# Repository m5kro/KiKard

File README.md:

# KiKard
Pronounced key card. KiKard is a usb microcontroller board with NFC read, write, and tag support. Built for Hack Club Highway. Not affiliated with KiCad (but do check them out).<br>
<br>

# What it does
KiKard is designed to read, write, and emulate NFC devices. This can be anything from simple link tags to complex keycards with custom communication standards. It can work independently or with a computer through BLE or USB.

# Why I built it
The goal of this project is to create a tool to assist me with my NFC application development learning. About a year ago, I wanted to make apps that utilize NFC, but I realized that most phones (most widespread implementation of NFC) are terrible for the development process as everything is very locked down. I did get a cheap PN532 reader from amazon and while it did help, it was still very lacking. Thus I decided to create KiKard to cover all the requirements needed by my other projects.

# Other Notes
Although the NRF has NFC support built in, it's only for tag mode, so a separate chip is needed for reading NFC.<br>
RGB LED 1 - Status led Green: just connected, Pink: reset/flashing, Blue: NRF52 tag mode, Yellow: ST25 read mode, Red: error<br>
RGB LED 2 - read/tag status Yellow: waiting, Blue: reading/emulating, Green: success, Red: error<br>
Button 1 - Read/emulate<br>
Button 2 - Switch between NRF52 and ST25<br>
Button 3 - Switch emulated tag (can save different cards on device)<br>
The DAPLINK is used to flash the NRF with a bootloader as it doesn't come with one by default. There are test pads on the board to connect.<br>
There are alot of extended parts as I needed high quality caps for the NFC antenna.<br>
Tariffs are making this project alot more expensive than it needs to be ;(

# Bom
| Item | Price |
| :-----: | :-----: |
| Custom PCB x5 | $4.00 |
| PCBA Setup | $8.00 |
| Stencil | $1.50 |
| PCB Parts x2| $20.07
| Extended Parts Fee | $81.00 |
| SMT Assembly | $1.86
| X-ray Inspection (required) | $3.14 |
| Nitrogen Reflow Soldering | $0.82 |
| Shipping | $28.85 |
| Customs | $66.22 |
| [DAPLINK](https://www.aliexpress.us/item/3256803753392042.html?spm=a2g0o.productlist.main.3.3b9aeQixeQixOW&algo_pvid=7bf879f9-2744-4cec-8234-a12f393fd66a&algo_exp_id=7bf879f9-2744-4cec-8234-a12f393fd66a-2&pdp_ext_f=%7B%22order%22%3A%2246%22%2C%22eval%22%3A%221%22%7D&pdp_npi=4%40dis%21USD%212.61%210.99%21%21%212.61%210.99%21%402101eac917534651461111152e6da5%2112000027518372890%21sea%21US%210%21ABX&curPageLogUid=WIV7fF3EkrpJ&utparam-url=scene%3Asearch%7Cquery_from%3A) | $3.52 |
| JLCPCB special discount | -$2.00 |

**Total: $227.50**

# PCB Parts Bom (PER PCB)
Total PCB Parts: 71<br>
Total PCB Parts Price (per PCB): $8.7174
| Part | Designator | Quantity | Price per Unit | Total | JLCPCB/LCSC Part No. |
| :---------: | :-----: | :-----: | :-----: | :-----: | :-----: |
| [NRF-52840-QIAA-R](https://jlcpcb.com/partdetail/NordicSemicon-NRF52840_QIAAR/C190794) | U1 | 1 | $4.0290 | $4.0290 | C190794 |
| [ST25R3916-AQWT](https://jlcpcb.com/partdetail/STMicroelectronics-ST25R3916AQWT/C2908147) | U2 | 1 | $3.3795 | $3.3795 | C2908147 |
| [WNM3013-3/TR](https://jlcpcb.com/partdetail/WILLSEMI_Will_Semicon-WNM3013_3TR/C239659) | Q1, Q2 | 2 | $0.0333 | $0.0667 | C239659 |
| [32MHz Crystal Oscillator](https://jlcpcb.com/partdetail/2777870-X201632MOB4SI/C2682773) | Y2 | 1 | $0.0890 | $0.0890 | C2682773 |
| [27MHz Crystal Oscillator](https://jlcpcb.com/partdetail/604049-XRCGB27M120F3M00R0/C576558) | Y1 | 1 | $0.1773 | $0.1773 | C576558 |
| [32KHz Crystal Oscillator](https://jlcpcb.com/partdetail/357119-X161032768KGD2SI/C383847) | Y3 | 1 | $0.3825 | $0.3825 | C383847 |
| [USB-C Port](https://jlcpcb.com/partdetail/SHOUHAN-TYPEC16PIN/C393939) | USB1 | 1 | $0.0642 | $0.0642 | C393939 |
| [RGBLED](https://jlcpcb.com/partdetail/ChauLight-ZSRGB_2017H_08Z3/C7497245) | LED1, LED2 | 2 | $0.0807 | $0.1614 | C7497245 |
| [Button](https://jlcpcb.com/partdetail/Korean_HropartsElec-K2_6639SP_C4SC04/C83206) | SW1, SW2, SW3 | 3 | $0.0380 | $0.1140 | C83206 |
| [Small Button](https://jlcpcb.com/partdetail/hanxia-HX_3x4x2_2P_25N/C36498961) | SW4 | 1 | $0.0299 | $0.0299 | C36498961 |
| [100k Ohm Resistor](https://jlcpcb.com/partdetail/YAGEO-RC0603FR07100KL/C14675) | R3, R4 | 2 | $0.0010 | $0.0020 | C14675 |
| [10k Ohm Resistor](https://jlcpcb.com/partdetail/26274-0402WGJ0103TCE/C25531) | R5 | 1 | $0.0004 | $0.0004 | C25531 |
| [5.1k Ohm Resistor](https://jlcpcb.com/partdetail/26684-0402WGJ0512TCE/C25941) | R1, R2 | 2 | $0.0004 | $0.0008 | C25941 |
| [4.7uF Capacitor](https://jlcpcb.com/partdetail/20375-CL10A475KO8NNNC/C19666) | C1, C2, C3, C32 | 4 | $0.0101 | $0.0404 | C19666 |
| [2.2uF Capacitor](https://jlcpcb.com/partdetail/1959-CL10A225KP8NNNC/C1607) | C5, C7, C9, C13, C15, C17, C19 | 7 | $0.0060 | $0.0420 | C1607 |
| [1uF Capacitor](https://jlcpcb.com/partdetail/15107-CL05A105KP5NNNC/C14445) | C11, C27 | 2 | $0.0016 | $0.0032 | C14445 |
| [100nF Capacitor](https://jlcpcb.com/partdetail/57421-0402B104K250NT/C56392) | C28, C29, C30, C31, C34, C47 | 6 |  $0.0011 |  $0.0066 | C56392 |
| [47nF Capacitor](https://jlcpcb.com/partdetail/83376-0402B473K500NT/C82219) | C26 | 1 | $0.0017 | $0.0017 | C82219 |
| [10nF Capacitor](https://jlcpcb.com/partdetail/1876-0402B103K500NT/C1524) | C4, C6, C8, C10, C12, C14, C16, C18 | 8 | $0.0010 | $0.0080 | C1524 |
| [1nF Capacitor](https://jlcpcb.com/partdetail/TDK-C1005C0G1E102JT000F/C343059) | C45, C46 | 2 | $0.0089 | $0.0178 | C343059 |
| [680pF Capacitor](https://jlcpcb.com/partdetail/1893-0402B681K500NT/C1541) | C38, C40 | 2 | $0.0011 | $0.0022 | C1541 |
| [100pF Capacitor](https://jlcpcb.com/partdetail/1898-0402CG101J500NT/C1546) | C35, C37, C41, C44 | 4 | $0.0089 | $0.0356 | C1546 |
| [62pF Capacitor](https://jlcpcb.com/partdetail/YAGEO-CC0402JRNPO9BN620/C281763) | C39, C42 | 2 | $0.0014 | $0.0028 | C281763 |
| [12pF Capacitor](https://jlcpcb.com/partdetail/1899-0402CG120J500NT/C1547) | C22, C23 | 2 | $0.0010 | $0.0020 | C1547 |
| [10pF Capacitor](https://jlcpcb.com/partdetail/1897-0402CG100J500NT/C1545) | C36, C43 | 2 | $0.0010 | $0.0020 | C1545 |
| [6pF Capacitor](https://jlcpcb.com/partdetail/1927-0402CG6R0C500NT/C1575) | C20, C21, C24, C25 | 4 | $0.0010 | $0.0040 | C1575 |
| [0.8pF Capacitor](https://jlcpcb.com/partdetail/41442-0402CG0R8C500NT/C40459) | C33 | 1 | $0.0013 | $0.0013 | C40459 |
| [10uH Inductor](https://jlcpcb.com/partdetail/Sunlord-MCL1608S100MT/C51942) | L1 | 1 | $0.0212 | $0.0212 | C51942 |
| [270nH Inductor](https://jlcpcb.com/partdetail/TDK-MLG1005SR27JT000/C76784) | L4, L5 | 2 | $0.0077 | $0.0154 | C76784 |
| [15nH Inductor](https://jlcpcb.com/partdetail/Sunlord-SDCL1608C15NJTDF/C23651) | L2 | 1 | $0.0106 | $0.0106 | C23651 |
| [3.9nH Inductor](https://jlcpcb.com/partdetail/Sunlord-SDCL1005C3N9STDF/C14033) | L3 | 1 | $0.0039 | $0.0039 | C14033 |

# Credit
[NRF-52840-QIAA-R schematic and footprint was aquired from snapeda](https://www.snapeda.com/parts/NRF52840-QIAA-R/Nordic%20Power/view-part/)<br>
[ST25R3916-AQWT schematic and footprint was aquired from snapeda](https://www.snapeda.com/parts/ST25R3916-AQWT/STMicroelectronics/view-part/)<br>
[NFC antenna footprint created using nfc antenna generator by nideri](https://github.com/nideri/nfc_antenna_generator)

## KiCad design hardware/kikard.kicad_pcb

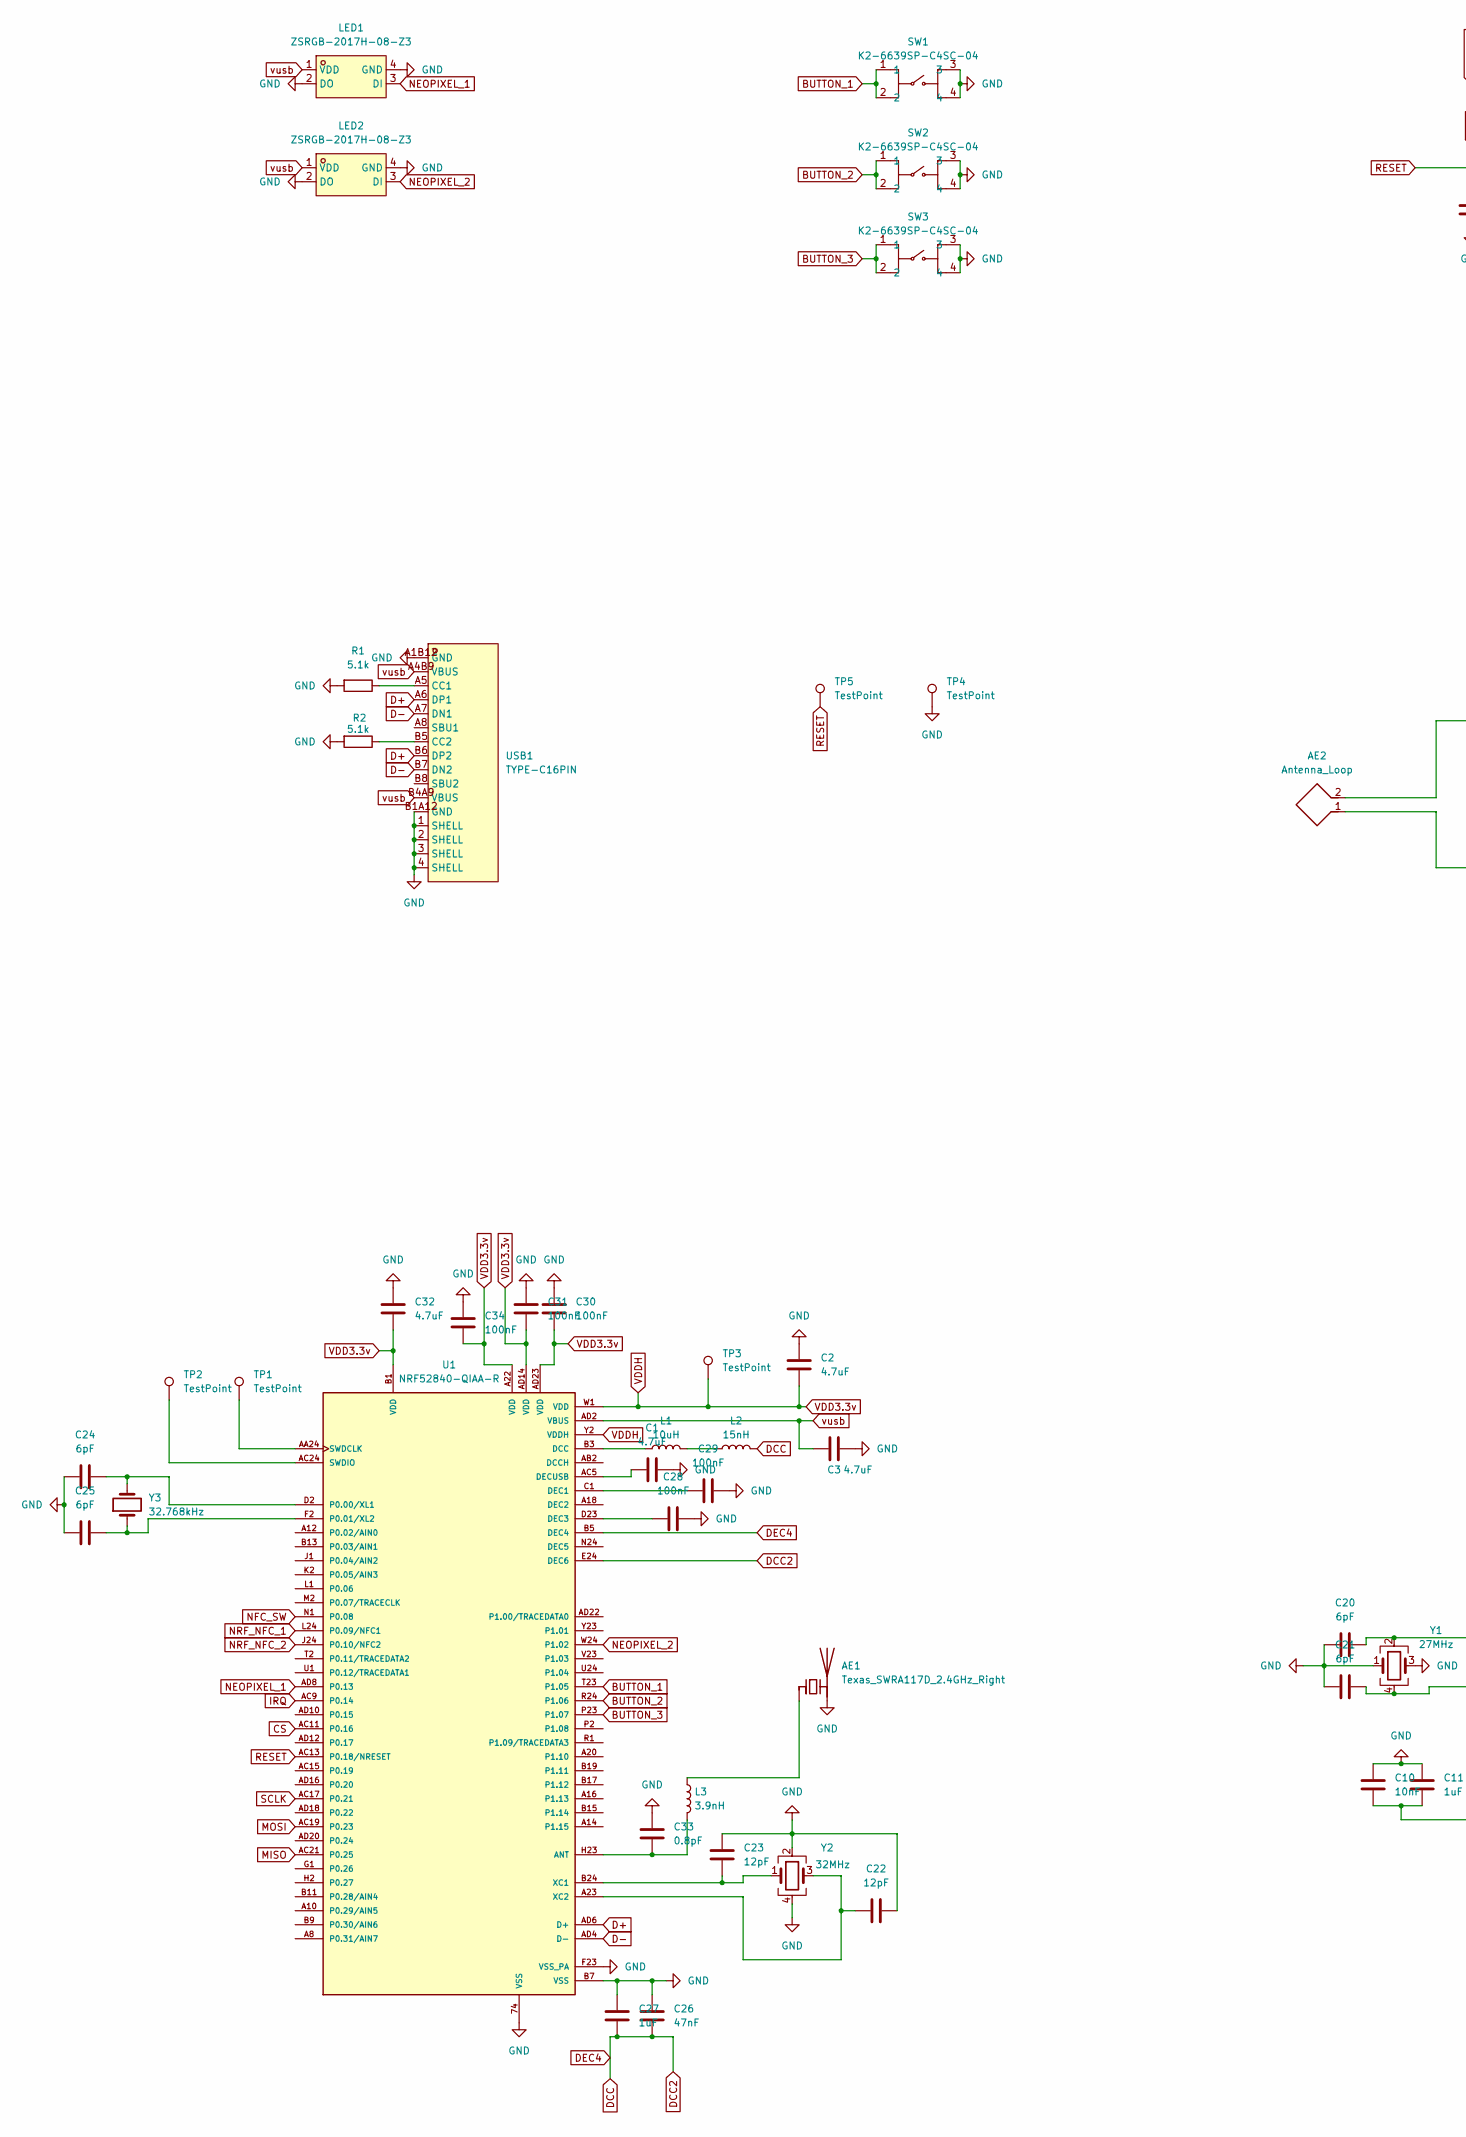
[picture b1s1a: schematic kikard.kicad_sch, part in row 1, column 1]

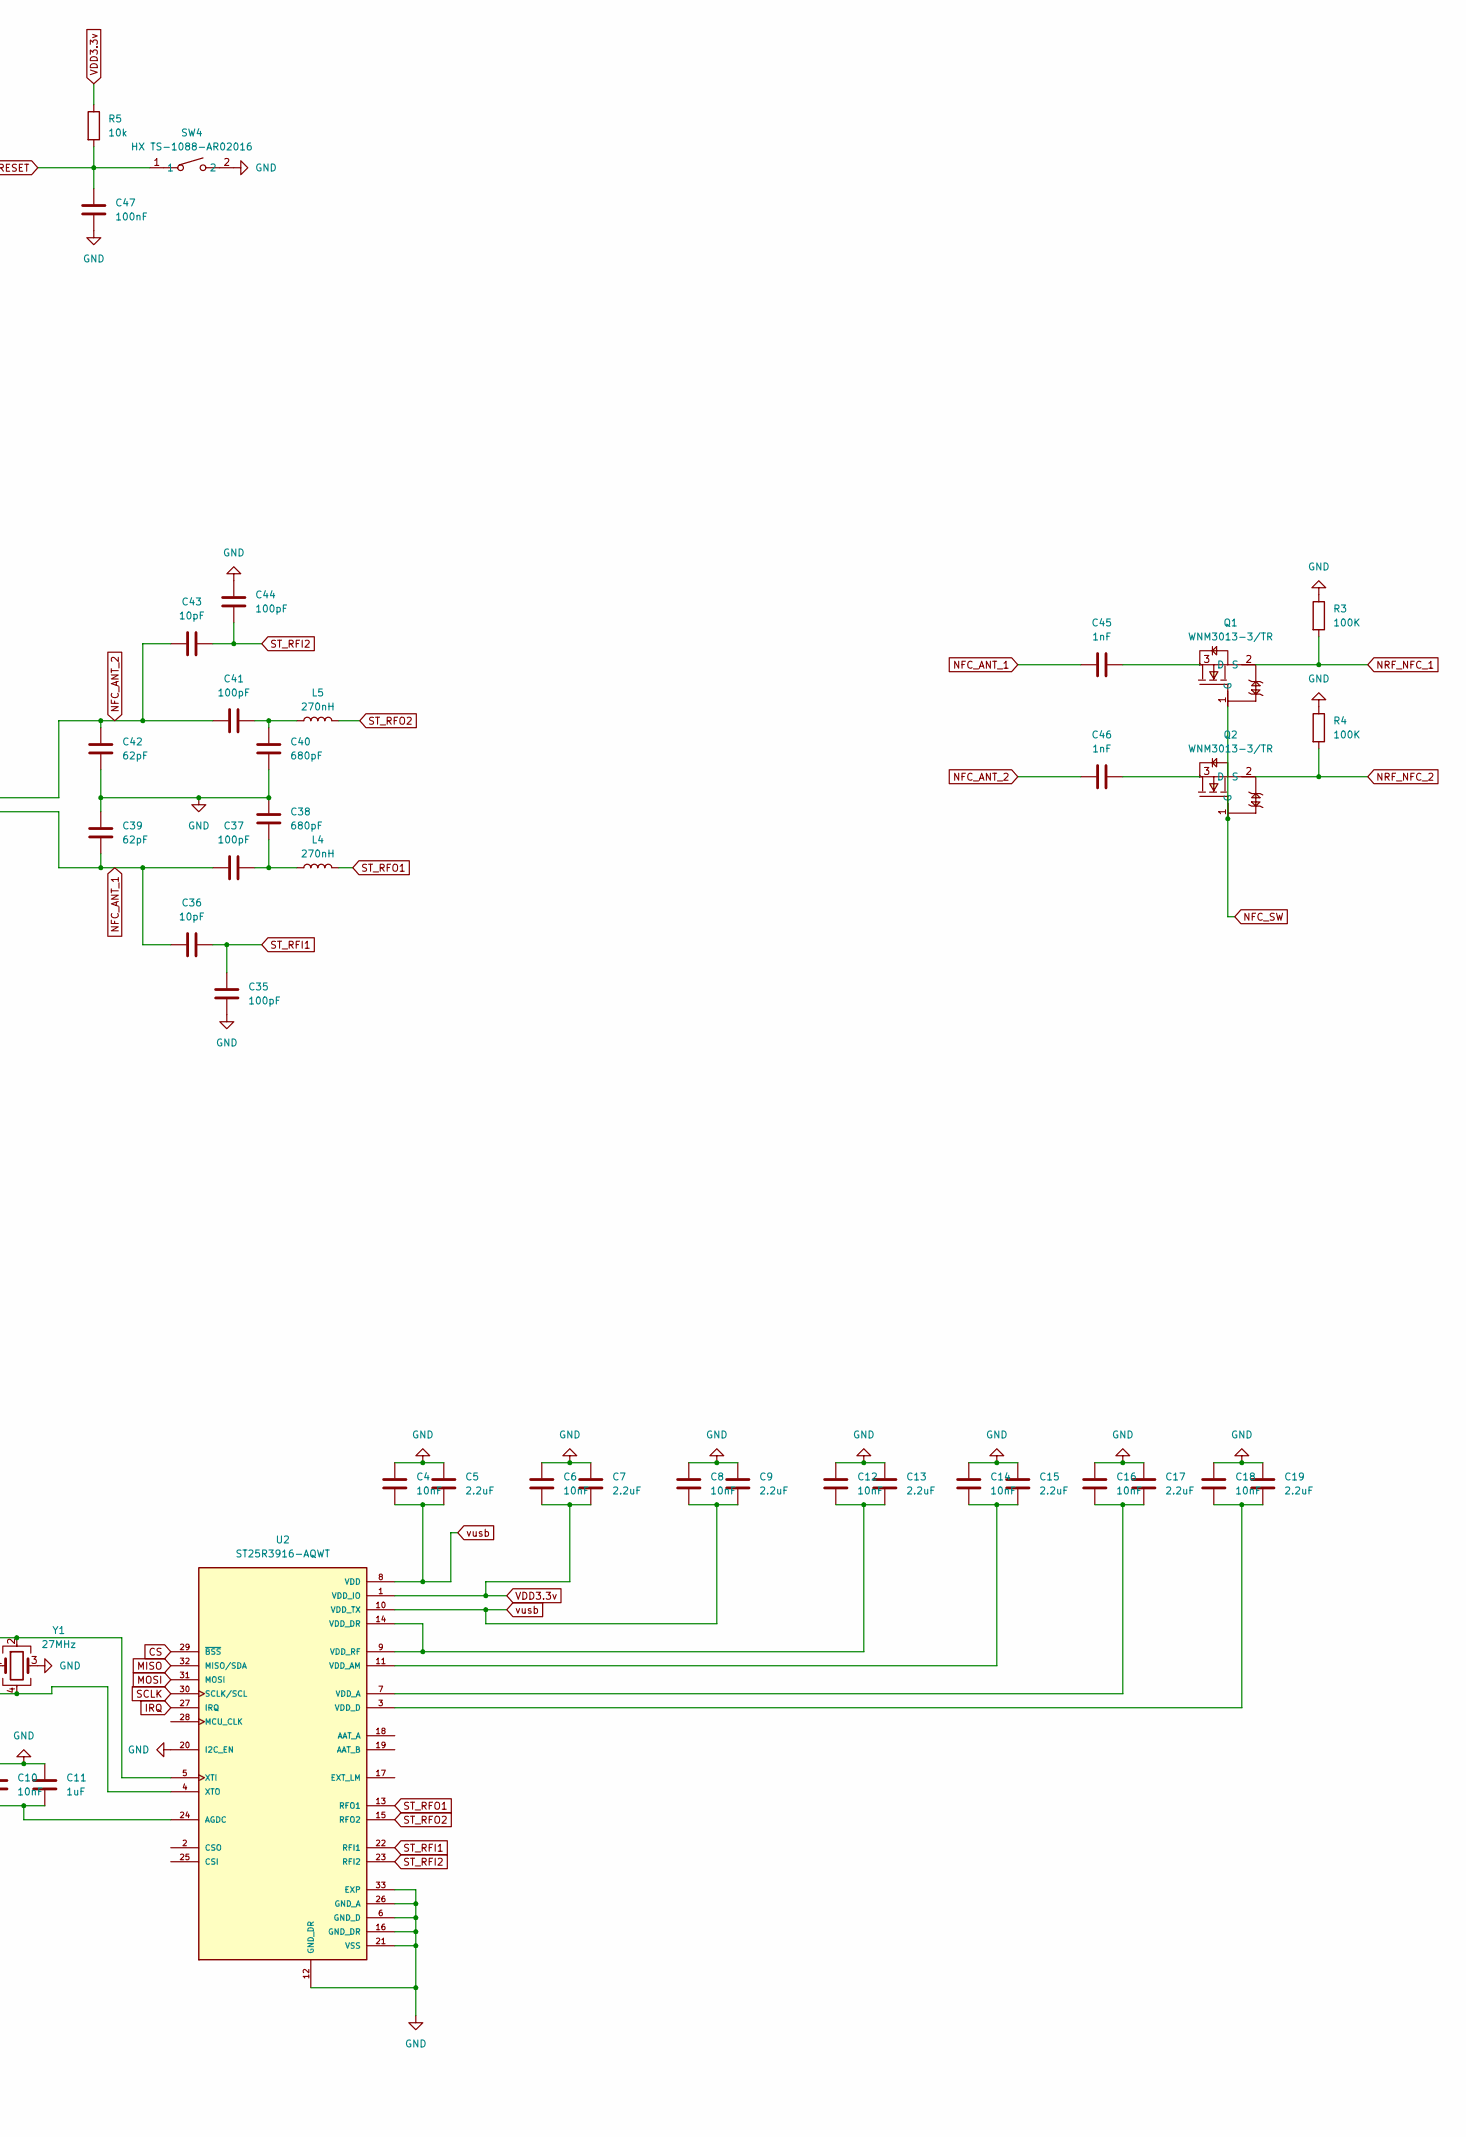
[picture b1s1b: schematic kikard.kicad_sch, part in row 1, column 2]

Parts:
AE1: Texas_SWRA117D_2.4GHz_Right
AE2: Antenna_Loop; kikard-ant-v1.0
C1, C2, C3, C32: 4.7uF; C0603
C4, C6, C8, C10, C12, C14, C16, C18: 10nF; C0402
C5, C7, C9, C13, C15, C17, C19: 2.2uF; C0603
C11, C27: 1uF; C0402
C20, C21, C24, C25: 6pF; C0402
C22, C23: 12pF; C0402
C26: 47nF; C0402
C28, C29, C30, C31, C34, C47: 100nF; C0402
C33: 0.8pF; C0402
C35, C37, C41, C44: 100pF; C0402
C36, C43: 10pF; C0402
C38, C40: 680pF; C0402
C39, C42: 62pF; C0402
C45, C46: 1nF; C0402
L1: 10uH; L0603
L2: 15nH; L0603
L3: 3.9nH; L0402
L4, L5: 270nH; L0402
LED1, LED2: ZSRGB-2017H-08-Z3; LED-SMD_4P-L2.0-W1.8-P0.90_XGM-S0807RGB; LCSC Part C7497245
Q1, Q2: WNM3013-3/TR; SOT-723_L1.2-W0.8-P0.40-LS1.2-BR; LCSC Part C239659
R1, R2: 5.1k; R0402
R3, R4: 100K; R0603
R5: 10k; R0402
SW1, SW2, SW3: K2-6639SP-C4SC-04; KEY-SMD_4P-L6.0-W6.0-P3.90-LS9.0; LCSC Part C83206
SW4: HX TS-1088-AR02016; SW-SMD_L4.0-W2.9-LS5.0; LCSC Part C36498961
TP1, TP2, TP3, TP4, TP5: TestPoint; TestPoint_Pad_D1.0mm
U1: NRF52840-QIAA-R; XCVR_NRF52840-QIAA-R; PARTREV v1.1
U2: ST25R3916-AQWT; QFN50P500X500X100-33N; PARTREV 4
USB1: TYPE-C16PIN; USB-C-SMD_TYPE-C16PIN; LCSC Part C393939
Y1: 27MHz; CRYSTAL-SMD_4P-L2.0-W1.6-BL-B
Y2: 32MHz; CRYSTAL-SMD_4P-L2.0-W1.6-BL-2
Y3: 32.768kHz; OSC-SMD_L1.6-W1.0

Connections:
BUTTON_1: SW1.1, SW1.2, U1.T23 (P1.05)
BUTTON_2: SW2.1, SW2.2, U1.R24 (P1.06)
BUTTON_3: SW3.1, SW3.2, U1.P23 (P1.07)
CS: U1.AC11 (P0.16), U2.29 (~BSS)
D+: U1.AD6 (D+), USB1.A6 (DP1), USB1.B6 (DP2)
D-: U1.AD4 (D-), USB1.A7 (DN1), USB1.B7 (DN2)
DCC: C26.2, C27.2, L2.2, U1.B5 (DEC4), U1.E24 (DEC6)
GND: AE1.2 (PCB_Trace), C1.1, C2.1, C3.2, C4.1, C5.1, C6.1, C7.1, C8.1, C9.1, C10.1, C11.1, C12.1, C13.1, C14.1, C15.1, C16.1, C17.1, C18.1, C19.1, C20.1, C21.1, C22.2, C23.2, C24.1, C25.1, C26.1, C27.1, C28.2, C29.2, C30.1, C31.1, C32.1, C33.1, C34.1, C35.2, C38.1, C39.1, C40.2, C42.2, C44.1, C47.2, LED1.2 (DO), LED1.4 (GND), LED2.2 (DO), LED2.4 (GND), R1.2, R2.2, R3.1, R4.1, SW1.3, SW1.4, SW2.3, SW2.4, SW3.3, SW3.4, SW4.2, TP4.1, U1.74 (VSS), U1.B7 (VSS), U1.F23 (VSS_PA), U2.6 (GND_D), U2.12 (GND_DR), U2.16 (GND_DR), U2.20 (I2C_EN), U2.21 (VSS), U2.26 (GND_A), U2.33 (EXP), USB1.1 (SHELL), USB1.2 (SHELL), USB1.3 (SHELL), USB1.4 (SHELL), USB1.A1B12 (GND), USB1.B1A12 (GND), Y1.1, Y1.3, Y2.2, Y2.4
IRQ: U1.AC9 (P0.14), U2.27 (IRQ)
MISO: U1.AC21 (P0.25), U2.32 (MISO/SDA)
MOSI: U1.AC19 (P0.23), U2.31 (MOSI)
NEOPIXEL_1: LED1.3 (DI), U1.AD8 (P0.13)
NEOPIXEL_2: LED2.3 (DI), U1.W24 (P1.02)
NFC_ANT_1: AE2.1, C36.1, C37.1, C39.2, C45.1
NFC_ANT_2: AE2.2, C41.1, C42.1, C43.1, C46.1
NFC_SW: Q1.1 (G), Q2.1 (G), U1.N1 (P0.08)
NRF_NFC_1: Q1.2 (S), R3.2, U1.L24 (P0.09/NFC1)
NRF_NFC_2: Q2.2 (S), R4.2, U1.J24 (P0.10/NFC2)
unnamed: AE1.1 (FEED), L3.1
unnamed: C37.2, C38.2, L4.1
unnamed: C40.1, C41.2, L5.1
unnamed: L1.2, L2.1
unnamed: C45.2, Q1.3 (D)
unnamed: C46.2, Q2.3 (D)
unnamed: C33.2, L3.2, U1.H23 (ANT)
unnamed: L1.1, U1.B3 (DCC)
unnamed: C29.1, U1.C1 (DEC1)
unnamed: C28.1, U1.D23 (DEC3)
unnamed: C1.2, U1.AC5 (DECUSB)
unnamed: C24.2, U1.D2 (P0.00/XL1), Y3.2
unnamed: C25.2, U1.F2 (P0.01/XL2), Y3.1
unnamed: TP1.1, U1.AA24 (SWDCLK)
unnamed: TP2.1, U1.AC24 (SWDIO)
unnamed: C23.1, U1.B24 (XC1), Y2.1
unnamed: C22.1, U1.A23 (XC2), Y2.3
unnamed: C10.2, C11.2, U2.24 (AGDC)
unnamed: C16.2, C17.2, U2.7 (VDD_A)
unnamed: C14.2, C15.2, U2.11 (VDD_AM)
unnamed: C18.2, C19.2, U2.3 (VDD_D)
unnamed: C12.2, C13.2, U2.9 (VDD_RF), U2.14 (VDD_DR)
unnamed: C20.2, U2.5 (XTI), Y1.2
unnamed: C21.2, U2.4 (XTO), Y1.4
unnamed: R1.1, USB1.A5 (CC1)
unnamed: R2.1, USB1.B5 (CC2)
RESET: C47.1, R5.2, SW4.1, TP5.1, U1.AC13 (P0.18/NRESET)
SCLK: U1.AC17 (P0.21), U2.30 (SCLK/SCL)
ST_RFI1: C35.1, C36.2, U2.22 (RFI1)
ST_RFI2: C43.2, C44.2, U2.23 (RFI2)
ST_RFO1: L4.2, U2.13 (RFO1)
ST_RFO2: L5.2, U2.15 (RFO2)
VDD3.3v: C2.2, C6.2, C7.2, C30.2, C31.2, C32.2, C34.2, R5.1, TP3.1, U1.A22 (VDD), U1.AD14 (VDD), U1.AD23 (VDD), U1.B1 (VDD), U1.W1 (VDD), U1.Y2 (VDDH), U2.1 (VDD_IO)
vusb: C3.1, C4.2, C5.2, C8.2, C9.2, LED1.1 (VDD), LED2.1 (VDD), U1.AD2 (VBUS), U2.8 (VDD), U2.10 (VDD_TX), USB1.A4B9 (VBUS), USB1.B4A9 (VBUS)

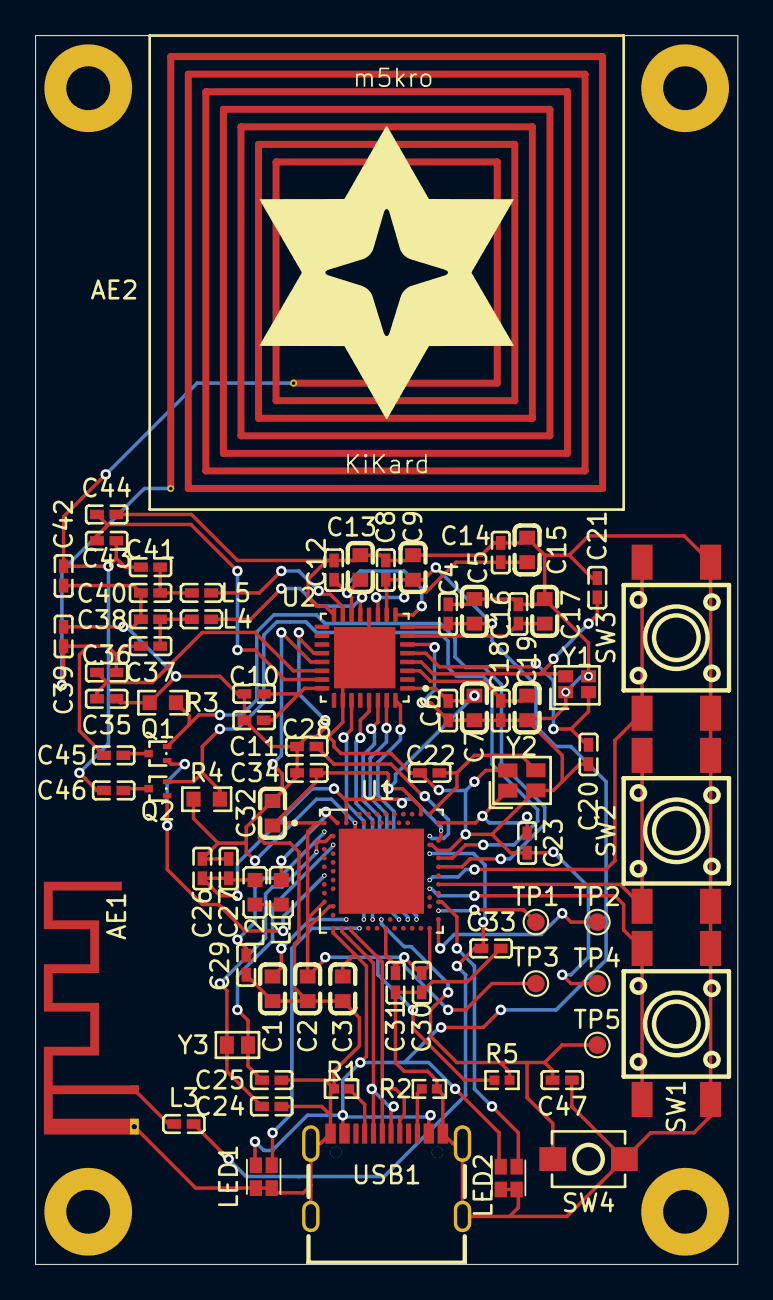
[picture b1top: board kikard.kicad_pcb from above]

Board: 2 copper layers, 40.0 x 70.0 mm, 78 parts (0 on the bottom side), 52 nets.

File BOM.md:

# Bom
| Item | Price |
| :-----: | :-----: |
| Custom PCB x5 | $4.00 |
| PCB Parts x5 | $44.43 |
| Extended Parts Fee | $81.00 |
| SMT Assembly | $2.90 |
| X-ray Inspection (required) | $7.85 |
| Nitrogen Reflow Soldering | $0.86 |
| Shipping | $9.04 |
| [DAPLINK](https://www.amazon.com/DAPLINK-Replaces-STLINK-downloader-Em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 | $5.14 |
| JLCPCB special discount | -$2.00 |
| JLCPCB Coupon | -$20.00 |

**Total: $142.72**

# PCB Parts Bom (PER PCB)
Total PCB Parts: 71<br>
Total PCB Parts Price (per PCB): $8.7174
| Part | Designator | Quantity | Price per Unit | Total | JLCPCB/LCSC Part No. |
| :---------: | :-----: | :-----: | :-----: | :-----: | :-----: |
| [NRF-52840-QIAA-R](https://jlcpcb.com/partdetail/NordicSemicon-NRF52840_QIAAR/C190794) | U1 | 1 | $4.0290 | $4.0290 | C190794 |
| [ST25R3916-AQWT](https://jlcpcb.com/partdetail/STMicroelectronics-ST25R3916AQ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 | U2 | 1 | $3.3795 | $3.3795 | C2908147 |
| [WNM3013-3/TR](https://jlcpcb.com/partdetail/WILLSEMI_Will_Semicon-WNM3013_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 | Q1, Q2 | 2 | $0.0333 | $0.0667 | C239659 |
| [32MHz Crystal Oscillator](https://jlcpcb.com/partdetail/2777870-X201632MOB4SI/C2682773) | Y2 | 1 | $0.0890 | $0.0890 | C2682773 |
| [27MHz Crystal Oscillator](https://jlcpcb.com/partdetail/604049-XRCGB27M120F3M00R0/C576558) | Y1 | 1 | $0.1773 | $0.1773 | C576558 |
| [32KHz Crystal Oscillator](https://jlcpcb.com/partdetail/357119-X161032768KGD2SI/C383847) | Y3 | 1 | $0.3825 | $0.3825 | C383847 |
| [USB-C Port](https://jlcpcb.com/partdetail/SHOUHAN-TYPEC16PIN/C393939) | USB1 | 1 | $0.0642 | $0.0642 | C393939 |
| [RGBLED](https://jlcpcb.com/partdetail/ChauLight-ZSRGB_2017H_08Z3/C7497245) | LED1, LED2 | 2 | $0.0807 | $0.1614 | C7497245 |
| [Button](https://jlcpcb.com/partdetail/Korean_HropartsElec-K2_6639SP_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 | SW1, SW2, SW3 | 3 | $0.0380 | $0.1140 | C83206 |
| [Small Button](https://jlcpcb.com/partdetail/hanxia-HX_3x4x2_2P_25N/C36498961) | SW4 | 1 | $0.0299 | $0.0299 | C36498961 |
| [100k Ohm Resistor](https://jlcpcb.com/partdetail/YAGEO-RC0603FR07100KL/C14675) | R3, R4 | 2 | $0.0010 | $0.0020 | C14675 |
| [10k Ohm Resistor](https://jlcpcb.com/partdetail/26274-0402WGJ0103TCE/C25531) | R5 | 1 | $0.0004 | $0.0004 | C25531 |
| [5.1k Ohm Resistor](https://jlcpcb.com/partdetail/26684-0402WGJ0512TCE/C25941) | R1, R2 | 2 | $0.0004 | $0.0008 | C25941 |
| [4.7uF Capacitor](https://jlcpcb.com/partdetail/20375-CL10A475KO8NNNC/C19666) | C1, C2, C3, C32 | 4 | $0.0101 | $0.0404 | C19666 |
| [2.2uF Capacitor](https://jlcpcb.com/partdetail/1959-CL10A225KP8NNNC/C1607) | C5, C7, C9, C13, C15, C17, C19 | 7 | $0.0060 | $0.0420 | C1607 |
| [1uF Capacitor](https://jlcpcb.com/partdetail/15107-CL05A105KP5NNNC/C14445) | C11, C27 | 2 | $0.0016 | $0.0032 | C14445 |
| [100nF Capacitor](https://jlcpcb.com/partdetail/57421-0402B104K250NT/C56392) | C28, C29, C30, C31, C34, C47 | 6 |  $0.0011 |  $0.0066 | C56392 |
| [47nF Capacitor](https://jlcpcb.com/partdetail/83376-0402B473K500NT/C82219) | C26 | 1 | $0.0017 | $0.0017 | C82219 |
| [10nF Capacitor](https://jlcpcb.com/partdetail/1876-0402B103K500NT/C1524) | C4, C6, C8, C10, C12, C14, C16, C18 | 8 | $0.0010 | $0.0080 | C1524 |
| [1nF Capacitor](https://jlcpcb.com/partdetail/TDK-C1005C0G1E102JT000F/C343059) | C45, C46 | 2 | $0.0089 | $0.0178 | C343059 |
| [680pF Capacitor](https://jlcpcb.com/partdetail/1893-0402B681K500NT/C1541) | C38, C40 | 2 | $0.0011 | $0.0022 | C1541 |
| [100pF Capacitor](https://jlcpcb.com/partdetail/1898-0402CG101J500NT/C1546) | C35, C37, C41, C44 | 4 | $0.0089 | $0.0356 | C1546 |
| [62pF Capacitor](https://jlcpcb.com/partdetail/YAGEO-CC0402JRNPO9BN620/C281763) | C39, C42 | 2 | $0.0014 | $0.0028 | C281763 |
| [12pF Capacitor](https://jlcpcb.com/partdetail/1899-0402CG120J500NT/C1547) | C22, C23 | 2 | $0.0010 | $0.0020 | C1547 |
| [10pF Capacitor](https://jlcpcb.com/partdetail/1897-0402CG100J500NT/C1545) | C36, C43 | 2 | $0.0010 | $0.0020 | C1545 |
| [6pF Capacitor](https://jlcpcb.com/partdetail/1927-0402CG6R0C500NT/C1575) | C20, C21, C24, C25 | 4 | $0.0010 | $0.0040 | C1575 |
| [0.8pF Capacitor](https://jlcpcb.com/partdetail/41442-0402CG0R8C500NT/C40459) | C33 | 1 | $0.0013 | $0.0013 | C40459 |
| [10uH Inductor](https://jlcpcb.com/partdetail/Sunlord-MCL1608S100MT/C51942) | L1 | 1 | $0.0212 | $0.0212 | C51942 |
| [270nH Inductor](https://jlcpcb.com/partdetail/TDK-MLG1005SR27JT000/C76784) | L4, L5 | 2 | $0.0077 | $0.0154 | C76784 |
| [15nH Inductor](https://jlcpcb.com/partdetail/Sunlord-SDCL1608C15NJTDF/C23651) | L2 | 1 | $0.0106 | $0.0106 | C23651 |
| [3.9nH Inductor](https://jlcpcb.com/partdetail/Sunlord-SDCL1005C3N9STDF/C14033) | L3 | 1 | $0.0039 | $0.0039 | C14033 |

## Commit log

2025-06-01 June 6 journal update
2025-06-01 fix typos
2025-06-01 Add journal images
2025-06-01 Add stuff from KiCad
2025-06-03 6-4-25
2025-06-03 fix typo
2025-06-03 move journal
2025-06-05 6-6-25
2025-06-05 add missing bits
2025-06-30 6-29-25
2025-07-09 7-9-25
2025-07-11 7-11-25
2025-07-14 7-14-25
2025-07-17 7-16-25
2025-07-18 7-17-25
2025-07-19 7-18-25
2025-07-22 7-21-25
2025-07-25 7-25-25
2025-07-25 update BOM
2025-07-25 ready to submit
2025-07-25 add schematic pdf
2025-07-25 upload test firmware src
2025-07-25 rearrange
2025-07-25 more rearranging
2025-07-26 Fix BLE ant
2025-07-26 fix ble ant images
2025-07-26 fix readme
